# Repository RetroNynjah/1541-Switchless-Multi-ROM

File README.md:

# Retroninja 1541 Switchless Multi-ROM
<br/>
A microcontroller based switchless ROM switcher for the Commodore 1541 disk drive.
Switch between stock CBM DOS, JiffyDOS and other ROMs by issuing commands from Basic.
No computer modifications or drive enclosure modifications needed. Completely reversible drive modification.

Read the user's guide for more information. 

# A new revision of this board has been released under the more generic name [Switchless Multi-ROM for 2364](https://github.com/RetroNynjah/Switchless-Multi-ROM-for-2364)

## WARNING!
There's a bug in the current revision of this design. The A16 address pin is incorrectly connected to a pure analog input on the ATmega and can't be controlled. This causes the address pin on the flash chip to float and the upper half of the ROM can't be used. If you are using this version you can only use the lower half of the ROM and the contents in the upper half needs to be an exact copy of the lower half. Another workaround could be to tie pin 2 of the flash chip or pin 19 of the ATmgea to GND using a bodge wire.

  <br/>

## BOM
 |Component|Pcs |Name|Comment|
 |:--------|---:|:---|:------|
 | SST39SF010A | 1 | IC1 | Flash. SST39SF020/040 should work too. PLCC-32 |
 | ATMEGA328P-AU | 1 | IC2 | Or compatible ATmega8/48/88/168/328 variants. TQFP-32 |
 | 74AHCT273NSR | 1 | IC4 | Flip-Flop SO-20 (5.3mm width) |
 | 74AHCT1G04 | 1 | IC5 | Inverter single gate SOT-23 |
 | 100nF ceramic capacitor | 4 | C1, C2, C3, C4 | 0805 |
 | 30pF ceramic capacitor | 2 | C5, C6 | 0805 - 22pF works too |
 | 10k resistor | 1 | R1 | 0805 |
 | 560R resistor | 1 | R2 | 0805 - LED current limiting resistor|
 | LED | 1 | D1 | 0805 |
 | ECS-160-20-3X-TR | 1 | XTAL1 | Crystal 16MHz |
 | 12 pin header | 2 | "IC3" | Male machined pin headers or flat headers. 2.54mm pitch. To fit DIL-24 socket. |
 | 6 pin header right-angled | 1 | JP1 | Optional 2.54mm pitch. For ISP programmer. |

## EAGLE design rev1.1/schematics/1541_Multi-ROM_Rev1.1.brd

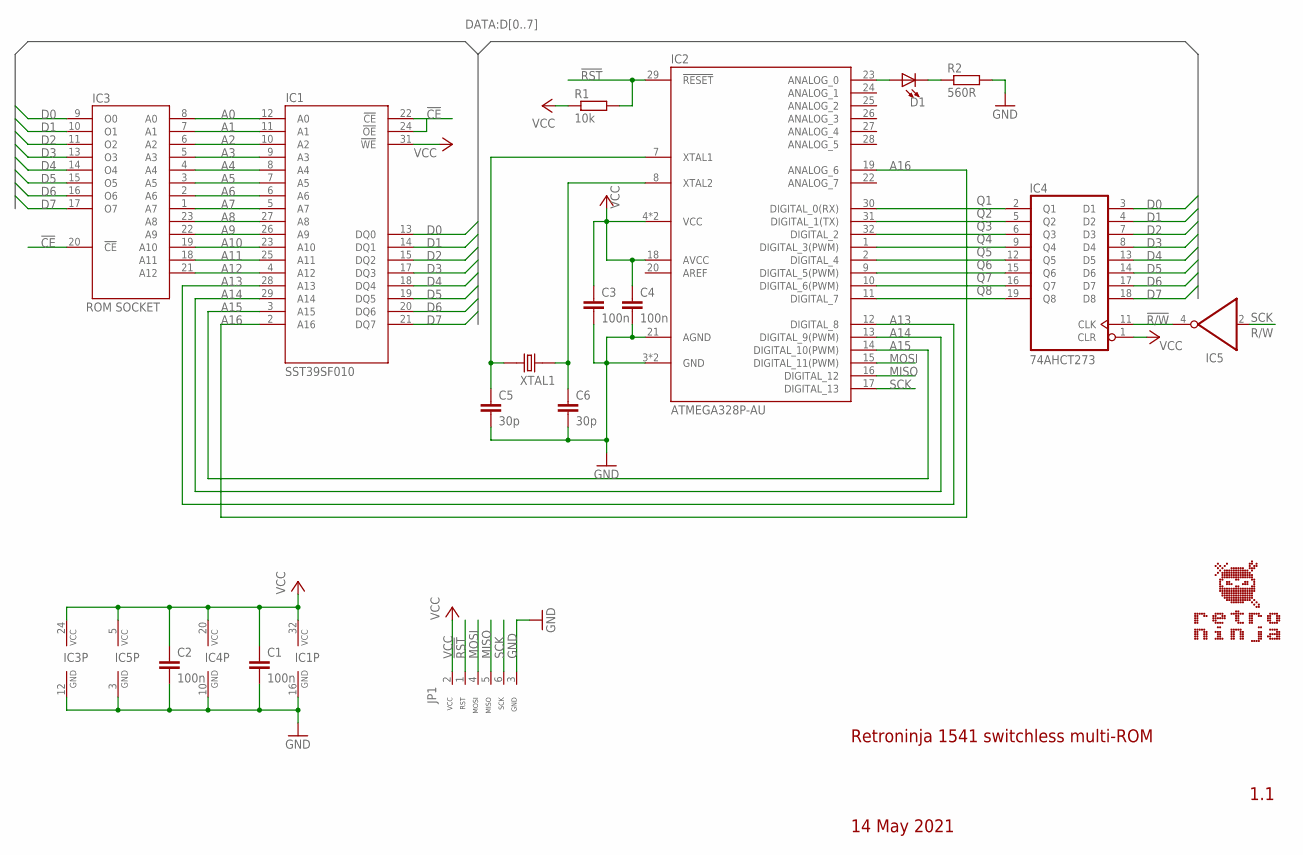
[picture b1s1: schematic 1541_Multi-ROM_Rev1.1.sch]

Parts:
C1, C2, C3, C4: 100n; C0805
C5, C6: 30p; C0805
D1: LED_0805; LED0805
IC1: SST39SF010; PLCC32_SHORT
IC2: ATMEGA328P-AU; TQFP32
IC3: ROM SOCKET; DIL24-6_DOWNPINS
IC4: 74AHCT273; SO20
IC5: 741G04_SOT23; SOT23-5
JP1: ICSP_CONNECTOR_TL866_RIGHT2; HEADER_1X6_RIGHT
R1: 10k; R0805
R2: 560R; R0805
XTAL1: CRYSTAL; CRYSTAL_SMD-2_7X4X2.3

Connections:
!CE: IC1.22 (!CE), IC3.20 (!CE)
!R/W: IC4.11 (CLK), IC5.4 (O)
!RST: IC2.29 (!RESET), JP1.1 (RST), R1.2
A0: IC1.12 (A0), IC3.8 (A0)
A1: IC1.11 (A1), IC3.7 (A1)
A2: IC1.10 (A2), IC3.6 (A2)
A3: IC1.9 (A3), IC3.5 (A3)
A4: IC1.8 (A4), IC3.4 (A4)
A5: IC1.7 (A5), IC3.3 (A5)
A6: IC1.6 (A6), IC3.2 (A6)
A7: IC1.5 (A7), IC3.1 (A7)
A8: IC1.27 (A8), IC3.23 (A8)
A9: IC1.26 (A9), IC3.22 (A9)
A10: IC1.23 (A10), IC3.19 (A10)
A11: IC1.25 (A11), IC3.18 (A11)
A12: IC1.4 (A12), IC3.21 (A12)
A13: IC1.28 (A13), IC2.12 (DIGITAL_8)
A14: IC1.29 (A14), IC2.13 (DIGITAL_9(PWM))
A15: IC1.3 (A15), IC2.14 (DIGITAL_10(PWM))
A16: IC1.2 (A16), IC2.19 (ANALOG_6)
D0: IC1.13 (DQ0), IC3.9 (O0), IC4.3 (D1)
D1: IC1.14 (DQ1), IC3.10 (O1), IC4.4 (D2)
D2: IC1.15 (DQ2), IC3.11 (O2), IC4.7 (D3)
D3: IC1.17 (DQ3), IC3.13 (O3), IC4.8 (D4)
D4: IC1.18 (DQ4), IC3.14 (O4), IC4.13 (D5)
D5: IC1.19 (DQ5), IC3.15 (O5), IC4.14 (D6)
D6: IC1.20 (DQ6), IC3.16 (O6), IC4.17 (D7)
D7: IC1.21 (DQ7), IC3.17 (O7), IC4.18 (D8)
GND: C1.2, C2.2, C3.2, C4.2, C5.2, C6.2, IC1.16 (GND), IC2.3 (GND), IC2.5 (GND), IC2.21 (AGND), IC3.12 (GND), IC4.10 (GND), IC5.3 (GND), JP1.3 (GND), R2.2
MISO: IC2.16 (DIGITAL_12), JP1.5 (MISO)
MOSI: IC2.15 (DIGITAL_11(PWM)), JP1.4 (MOSI)
unnamed: C6.1, IC2.8 (XTAL2), XTAL1.1
unnamed: C5.1, IC2.7 (XTAL1), XTAL1.2
unnamed: D1.A, IC2.23 (ANALOG_0)
unnamed: D1.C, R2.1
Q1: IC2.30 (DIGITAL_0(RX)), IC4.2 (Q1)
Q2: IC2.31 (DIGITAL_1(TX)), IC4.5 (Q2)
Q3: IC2.32 (DIGITAL_2), IC4.6 (Q3)
Q4: IC2.1 (DIGITAL_3(PWM)), IC4.9 (Q4)
Q5: IC2.2 (DIGITAL_4), IC4.12 (Q5)
Q6: IC2.9 (DIGITAL_5(PWM)), IC4.15 (Q6)
Q7: IC2.10 (DIGITAL_6(PWM)), IC4.16 (Q7)
Q8: IC2.11 (DIGITAL_7), IC4.19 (Q8)
SCK: IC2.17 (DIGITAL_13), IC5.2 (I), JP1.6 (SCK)
VCC: C1.1, C2.1, C3.1, C4.1, IC1.31 (!WE), IC1.32 (VCC), IC2.4 (VCC), IC2.6 (VCC), IC2.18 (AVCC), IC3.24 (VCC), IC4.1 (CLR), IC4.20 (VCC), IC5.5 (VCC), JP1.2 (VCC), R1.1

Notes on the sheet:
R/W
Retroninja 1541 switchless multi-ROM
1.1
14 May 2021

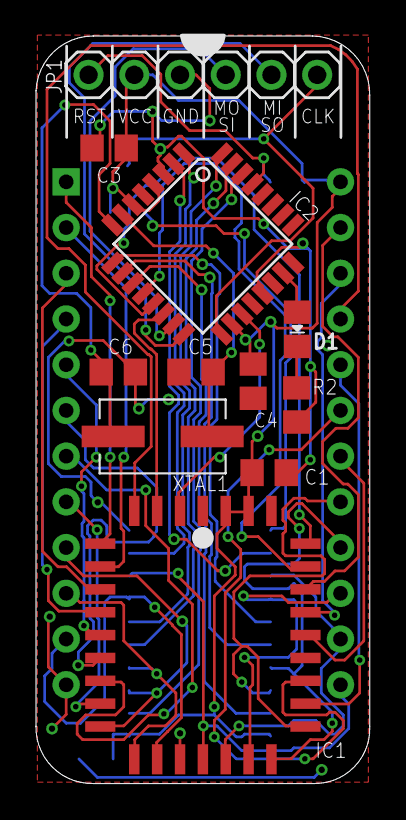
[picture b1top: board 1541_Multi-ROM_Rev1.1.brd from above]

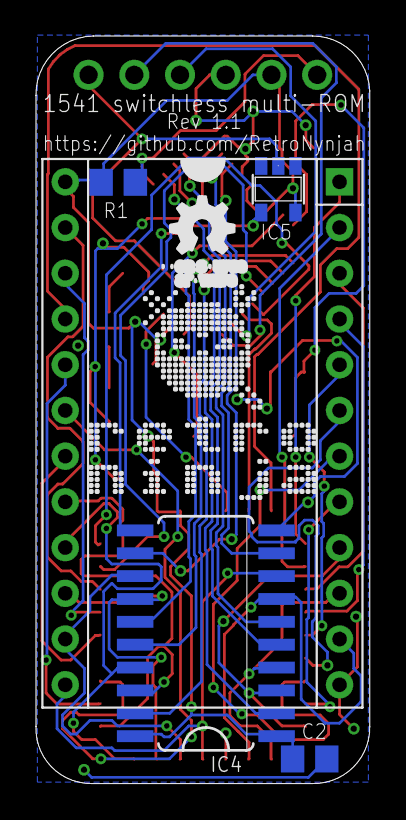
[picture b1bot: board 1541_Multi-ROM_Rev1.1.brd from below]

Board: 2 copper layers, 18.5 x 41.5 mm, 18 parts (6 on the bottom side), 45 nets.

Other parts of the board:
U$1: RETRONINJA_12MM
U$2: OSHW_5MM

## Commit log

2021-05-14 Renders updated
2021-05-15 Added images
2021-05-15 Update README.md
    Updated PCB images
2021-05-15 Update README.md
    Adjusted BOM
2021-05-22 Updated README and User's Guide
    Updated information about parts, MCU's and programming. User's guide change history section added.
2021-06-24 Update README.md
    Bug warning
